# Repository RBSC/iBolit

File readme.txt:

--------------------------------------------------------------------------------
iBolit Simple Diagnostics Cartridge
Copyright (c) 2020-2022 RBSC
Last updated: 16.07.2022
--------------------------------------------------------------------------------

UPDATE from 16.07.2022
----------------------

It's recommended to update the cartridge with an overvoltage protection. See the "iBolit_fuse.jpg" image in the Pics folder!

To install the overvoltage protection, isolate pin 24 of IC1 - cut the traces on both sides of the pin. Then purchase and
solder a 5.1V 1W rated zener diode between pins 12 and 24, the cathode should be connected to pin 24. Solder resettable fuse
0.5A between C2 and pin 24 of IC1. Solder a wire between C5 and the cut off trace to supply power to the voltmeters.

This way the PLD ICs and LEDs will be protected from the overvoltage while the 5V voltmeter will show exact voltage on the slot
connector.

About
-----

iBolit is a simple diagnostics cartridge. During the previous years we've seen numerous messages from MSX users, whose computers
suddenly stopped working after being removed from the storage or after another power cycle. Many people complained about black
screens or about total power failure. It's a known fact that RAM and other elements may go bad during storing or at power-on.
Diagnosing those problems usually starts from checking the power rails, clock signals, reset signal's state and activity on data
and address bus. It has been decided to create a simple diagnostics cartridge that could help to perform the initial check of a
computer and rule out the most common problems.

The cartridge that we named "iBolit" ( see Doctor Aybolit) was created using the GAL22V10 programmable logic chips, LED assemblies
and volt/ammeters from the PC's USB socket tester dongles. There's a cartridge slot installed on the top of iBolit cartridge's
board. There one can insert any cartridge including the one with MSX diagnostics ROM (there are a few, but it would be nice to
create a universal one). The GAL firmware is very primitive - if there's a high level on input, the LED connected to the output
will light up. The cartridge is fairly cheap to build - maximum 12-15 Euro - and is relatively easy to assemble. The daughterboard
with voltmeters is detachable.

Where to buy parts
------------------

The parts for assembling the cartridge can be purchased from these sellers on AliExpress:

 - https://www.aliexpress.com/item/32929139598.html   (buy the one with gray case and USB connectors on the left and right side)
 - https://www.aliexpress.com/item/4000078359420.html (buy 2 converters)
 - https://www.aliexpress.com/item/4001336380255.html (buy 2x5 pin headers)
 - https://www.aliexpress.com/item/32890057619.html   (buy 2x5 pin connectors)
 - https://www.aliexpress.com/item/4000970562846.html (also buy blue and yellow colors)
 - https://www.aliexpress.com/item/32800771545.html   (or use a different 5mm LED)
 - https://www.aliexpress.com/item/32918831775.html   (buy 1kOhm SMD resistor assemblies)
 - https://www.aliexpress.com/item/32948284513.html   (this LED is for the -12v voltmeter)
 - https://www.aliexpress.com/item/32375666910.html   (buy 10uF and 47uF capacitors)
 - https://www.aliexpress.com/item/4001146953252.html (buy 50-pin angled slot connector)

Assembling notes
----------------

Please read the following notes carefully:

 - It's highly recommended to install ceramic capacitors everywhere on the board. For the DC-DC converters the ceramic 10uF
   capacitors are a must

 - To adapt the voltmeters to work with iBolit, you need to first carefully open the USB tester's case with a knife and remove
   the board. Then desolder both indicator panels (mark one indicator panel to know where it came from) and desolder both USB
   connectors from the board. After that solder the indicator panels back to the board, but as low as possible. And finally
   solder two 4-pin pin headers to the board, the pins will have to be forces into the board because the distance between the
   holes is not 2.54mm

 - The voltmeter with a separate red LED is for -12v, it should be installed on the lowest position of the daughterboard. See
   the reference images

 - To install a small red LED to the -12v voltmeter (this step is optional), solder the cathode to the upper GND track and
   anode to the second pin from the top. See the reference images. The LED should be a bit above the voltmeter's board

 - Please note that LED assemblies may have incorrect key position! So please always test the LED assemblies with multimeter
   in the diode testing mode to find the correct polarity. The cathode should be on the right, like marked on the board

 - The pins of both DC-DC converters should be carefully bent at 90 degree angle and the converters have to be installed
   face-down. See the reference images

 - The GAL chips need to be programmed with the firmware before use. A widespread TL866 programmer will do just fine. Use
   the .JED firmware file from the "Firmware" folder and the "GAL22V10D" chip type when programming

 - Instead of one blue and two red LED assemblies you might want to install one red and two blue LED assemblies. Make your
   own choice. It's recommended to install the yellow LED assembly at the rightmost position. If you are installing the
   green LED assembly, you need to select a different value for the resistor assembly, for example 330 Ohm instead of 1kOhm

 - Before inserting the diagnostics board into the MSX slot it's highly recommend to make sure that +5v on the slot is within
   acceptable range (not more than 6-7v!), otherwise the diagnostics board may be damaged. The device doesn't have the
   over-voltage protection on the +5v rail

 - The daughterboard with voltmeters is detachable. When it is detached, no power will be supplied to the upper cartridge slot.
   If you need to use the cartridge slot without the attached daughterboard, you need to put 5 jumpers horizontally on 5 pairs
   of pins of the connector

IMPORTANT!
----------

The RBSC provides all the files and information for free, without any liability (see the disclaimer.txt file). The provided information,
software or hardware must not be used for commercial purposes unless permitted by the RBSC. Producing a small amount of bare boards for
personal projects and selling the rest of the batch is allowed without the permission of RBSC.

When the sources of the tools are used to create alternative projects, please always mention the original source and the copyright!

Contact information
-------------------

The members of RBSC group Tnt23, Wierzbowsky, Pencioner, Ptero, GreyWolf, SuperMax and DJS3000 can be contacted via the group's e-mail
address:

info@rbsc.su

The group's coordinator could be reached via this e-mail address:

admin@rbsc.su

The group's website can be found here:

https://rbsc.su/
https://rbsc.su/ru

The RBSC's hardware repository can be found here:

https://github.com/rbsc

The RBSC's 3D model repository can be found here:

https://www.thingiverse.com/groups/rbsc/things

-= ! MSX FOREVER ! =-

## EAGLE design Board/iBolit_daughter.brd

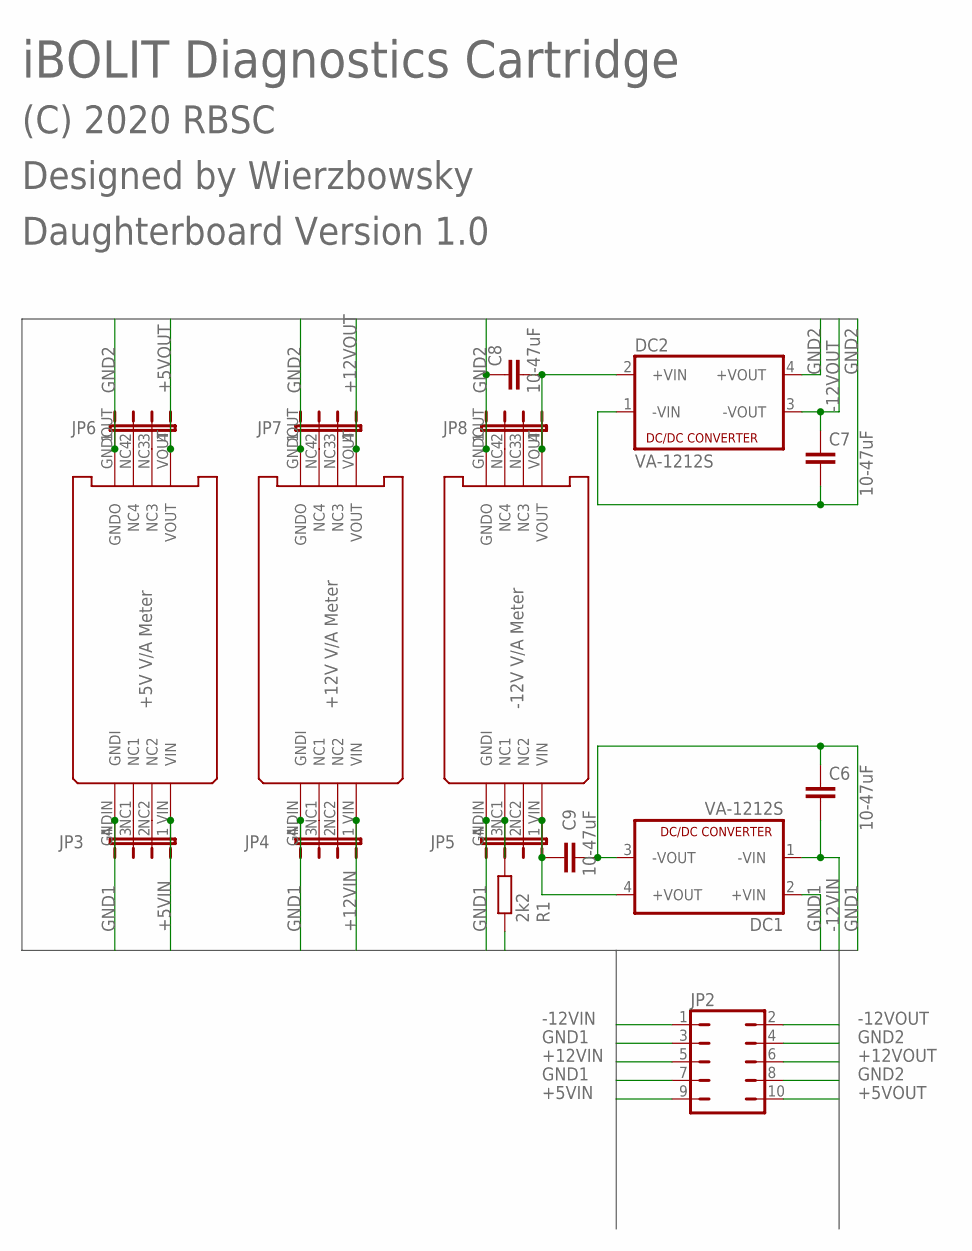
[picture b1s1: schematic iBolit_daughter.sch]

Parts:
C6, C7, C8, C9: 10-47uF; C1210
DC1, DC2: VA-1212S; 4SIL
JP2: JP5Q_CUSTOM
JP3, JP4, JP5, JP6, JP7, JP8: JP4E_CUSTOM; JP4_CUSTOM
R1: 2k2; R0805
X1, X2, X3: VA-METER; VA_METER

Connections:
+5VIN: JP2.9, JP3.1, R1.1, X1.VIN
+5VOUT: JP2.10, JP6.4, X1.VOUT
+12VCONVI: C9.1, DC1.4 (+VOUT), JP5.1, X3.VIN
+12VCONVO: C8.2, DC2.2 (+VIN), JP8.4, X3.VOUT
+12VIN: JP2.5, JP4.1, X2.VIN
+12VOUT: JP2.6, JP7.4, X2.VOUT
-12VIN: C6.2, DC1.1 (-VIN), JP2.1
-12VOUT: C7.1, DC2.3 (-VOUT), JP2.2
GND1: C6.1, C9.2, DC1.2 (+VIN), DC1.3 (-VOUT), JP2.3, JP2.7, JP3.4, JP4.4, JP5.4, X1.GNDIN (GNDI), X2.GNDIN (GNDI), X3.GNDIN (GNDI)
GND2: C7.2, C8.1, DC2.1 (-VIN), DC2.4 (+VOUT), JP2.4, JP2.8, JP6.1, JP7.1, JP8.1, X1.GNDOUT (GNDO), X2.GNDOUT (GNDO), X3.GNDOUT (GNDO)
unnamed: JP8.2, X3.NC4
unnamed: JP8.3, X3.NC3
unnamed: JP5.2, X3.NC2
unnamed: JP5.3, R1.2, X3.NC1
unnamed: JP4.2, X2.NC2
unnamed: JP3.2, X1.NC2
unnamed: JP3.3, X1.NC1
unnamed: JP6.2, X1.NC4
unnamed: JP6.3, X1.NC3
unnamed: JP7.2, X2.NC4
unnamed: JP7.3, X2.NC3
unnamed: JP4.3, X2.NC1

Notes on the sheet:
+5V V/A Meter
+12V V/A Meter
-12V V/A Meter
iBOLIT Diagnostics Cartridge
(C) 2020 RBSC
Designed by Wierzbowsky
Daughterboard Version 1.0

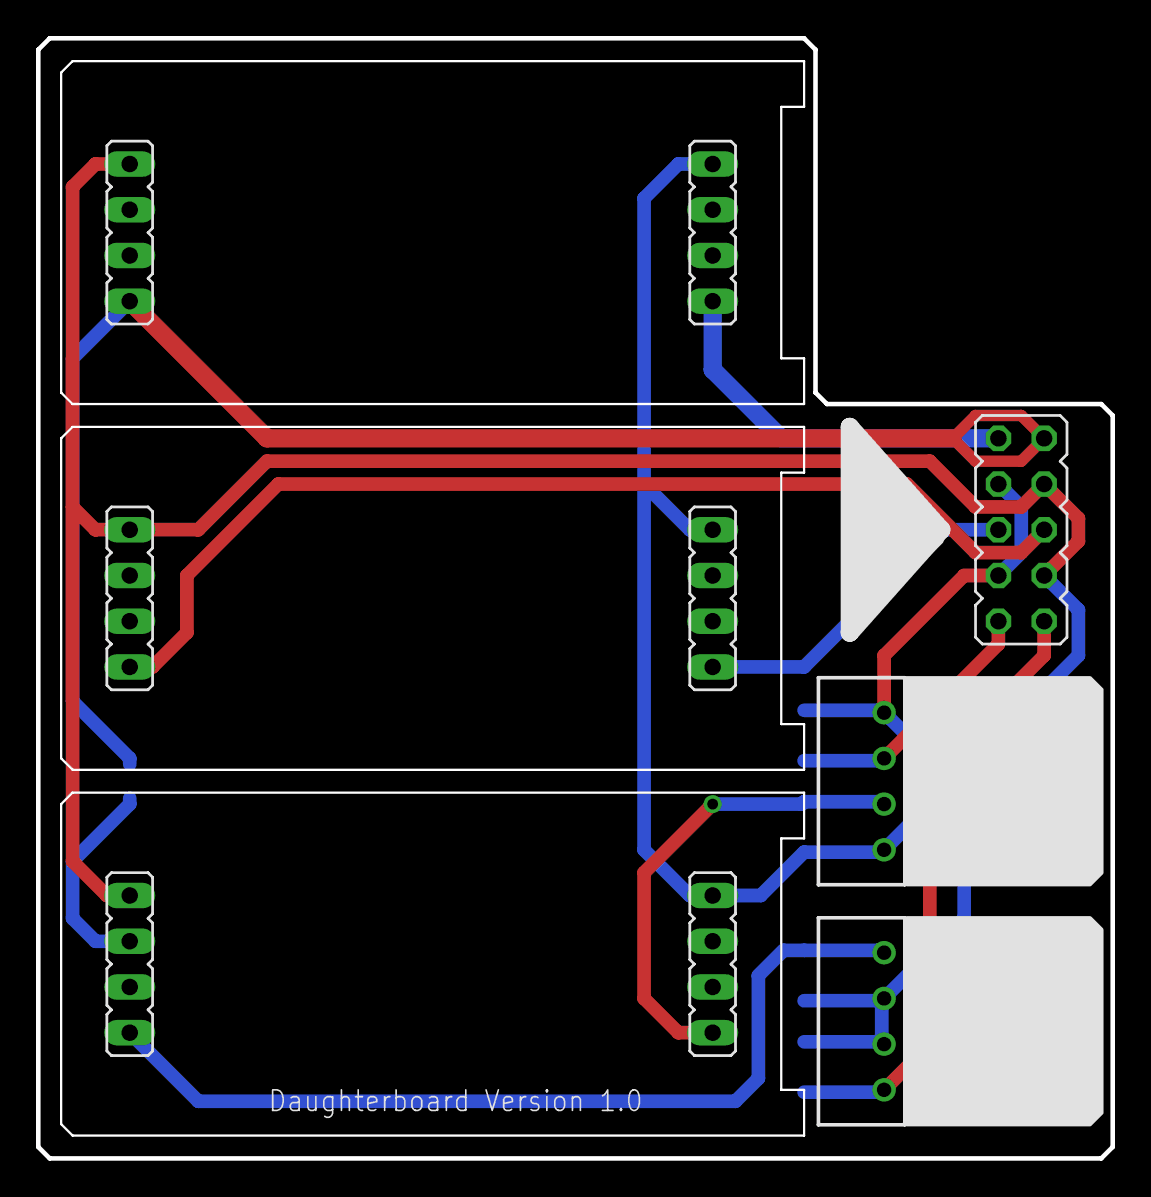
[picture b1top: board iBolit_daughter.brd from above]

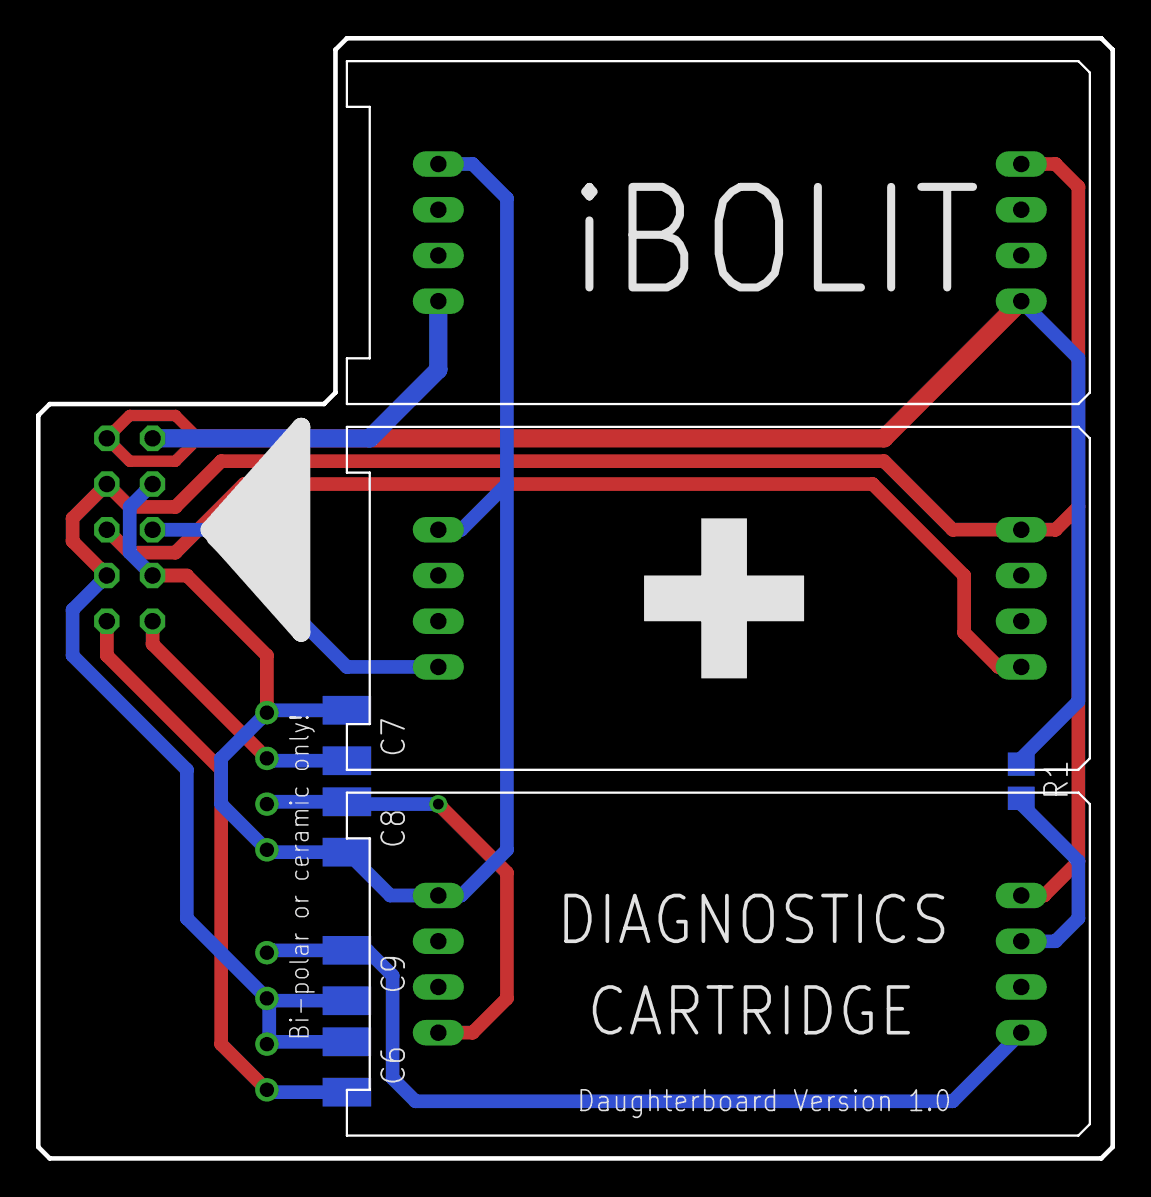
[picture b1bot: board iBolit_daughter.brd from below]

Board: 2 copper layers, 59.7 x 62.2 mm, 17 parts (5 on the bottom side), 22 nets.

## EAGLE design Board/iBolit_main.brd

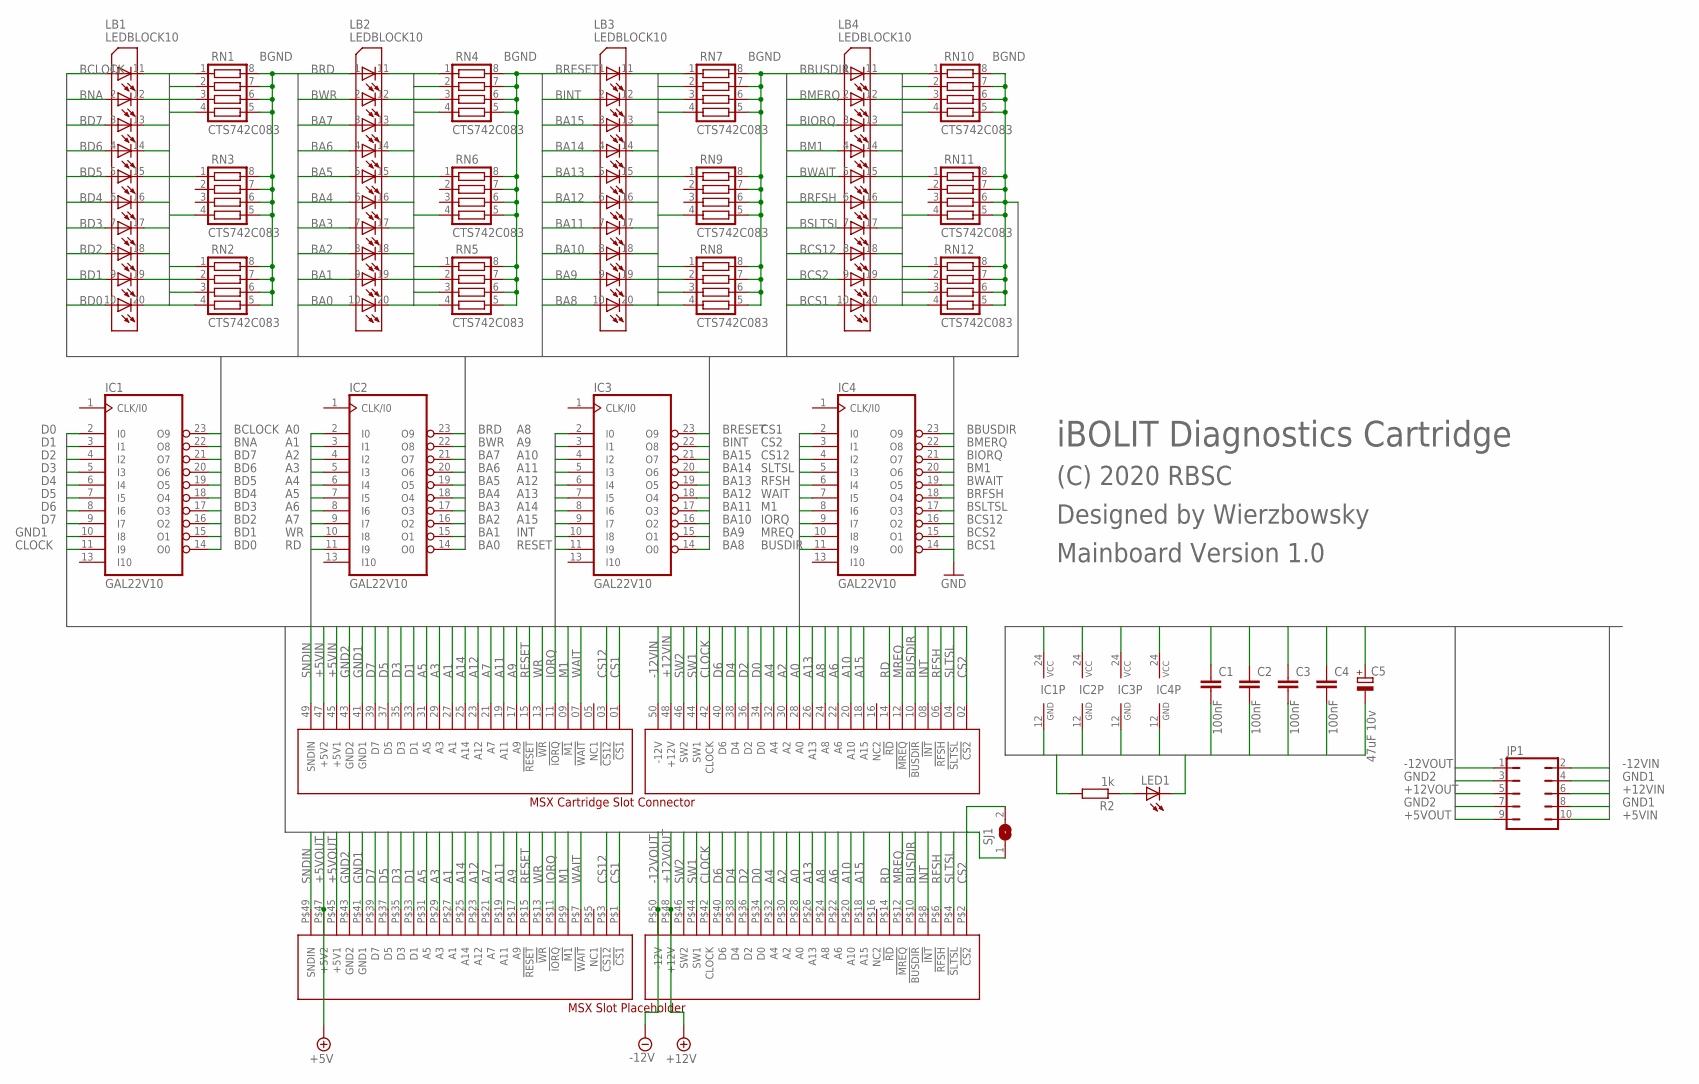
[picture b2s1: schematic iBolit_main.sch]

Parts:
C1, C2, C3, C4: 100nF; C0805
C5: 47uF 10v; SMC_B
CN1: SLOTCONN; MSX_SLOT_CON
CN2: SLOTPLACEHOLDER; MSX_SLOT_PLP
IC1, IC2, IC3, IC4: GAL22V10; DIL24-3
JP1: JP5Q_CUSTOM
LB1, LB2, LB3, LB4: LEDBLOCK10; LB10
LED1: LED5MM
R2: 1k; R0805
RN1, RN2, RN3, RN4, RN5, RN6, RN7, RN8, RN9, RN10, RN11, RN12: CTS742C083
SJ1: SJ

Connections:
1: LB1.11 (L1O), RN1.4
1A: LB2.11 (L1O), RN4.4
1B: LB3.11 (L1O), RN7.4
1C: LB4.11 (L1O), RN10.4
2: LB1.12 (L1O1), RN1.3
2A: LB2.12 (L1O1), RN4.3
2B: LB3.12 (L1O1), RN7.3
2C: LB4.12 (L1O1), RN10.3
3: LB1.13 (L1O2), RN1.2
3A: LB2.13 (L1O2), RN4.2
3B: LB3.13 (L1O2), RN7.2
3C: LB4.13 (L1O2), RN10.2
4: LB1.14 (L1O3), RN1.1
4A: LB2.14 (L1O3), RN4.1
4B: LB3.14 (L1O3), RN7.1
4C: LB4.14 (L1O3), RN10.1
5: LB1.15 (L1O4), RN3.4
5A: LB2.15 (L1O4), RN6.4
5B: LB3.15 (L1O4), RN9.4
5C: LB4.15 (L1O4), RN11.4
6: LB1.16 (L1O5), RN3.1
6A: LB2.16 (L1O5), RN6.1
6B: LB3.16 (L1O5), RN9.1
6C: LB4.16 (L1O5), RN11.1
7: LB1.17 (L1O6), RN2.4
7A: LB2.17 (L1O6), RN5.4
7B: LB3.17 (L1O6), RN8.4
7C: LB4.17 (L1O6), RN12.4
8: LB1.18 (L1O7), RN2.3
8A: LB2.18 (L1O7), RN5.3
8B: LB3.18 (L1O7), RN8.3
8C: LB4.18 (L1O7), RN12.3
9: LB1.19 (L1O8), RN2.2
9A: LB2.19 (L1O8), RN5.2
9B: LB3.19 (L1O8), RN8.2
9C: LB4.19 (L1O8), RN12.2
10: LB1.20 (L1O9), RN2.1
10A: LB2.20 (L1O9), RN5.1
10B: LB3.20 (L1O9), RN8.1
10C: LB4.20 (L1O9), RN12.1
+5VIN: C1.1, C2.1, C3.1, C4.1, C5.+, CN1.45 (+5V1), CN1.47 (+5V2), IC1.24 (VCC), IC2.24 (VCC), IC3.24 (VCC), IC4.24 (VCC), JP1.10, R2.2
+5VOUT: CN2.P$45 (+5V1), CN2.P$47 (+5V2), JP1.9
+12VIN: CN1.48 (+12V), JP1.6
+12VOUT: CN2.P$48 (+12V), JP1.5
-12VIN: CN1.50 (-12V), JP1.2
-12VOUT: CN2.P$50 (-12V), JP1.1
A0: CN1.28 (A0), CN2.P$28 (A0), IC2.2 (I0)
A1: CN1.27 (A1), CN2.P$27 (A1), IC2.3 (I1)
A2: CN1.30 (A2), CN2.P$30 (A2), IC2.4 (I2)
A3: CN1.29 (A3), CN2.P$29 (A3), IC2.5 (I3)
A4: CN1.32 (A4), CN2.P$32 (A4), IC2.6 (I4)
A5: CN1.31 (A5), CN2.P$31 (A5), IC2.7 (I5)
A6: CN1.22 (A6), CN2.P$22 (A6), IC2.8 (I6)
A7: CN1.21 (A7), CN2.P$21 (A7), IC2.9 (I7)
A8: CN1.24 (A8), CN2.P$24 (A8), IC3.2 (I0)
A9: CN1.17 (A9), CN2.P$17 (A9), IC3.3 (I1)
A10: CN1.20 (A10), CN2.P$20 (A10), IC3.4 (I2)
A11: CN1.19 (A11), CN2.P$19 (A11), IC3.5 (I3)
A12: CN1.23 (A12), CN2.P$23 (A12), IC3.6 (I4)
A13: CN1.26 (A13), CN2.P$26 (A13), IC3.7 (I5)
A14: CN1.25 (A14), CN2.P$25 (A14), IC3.8 (I6)
A15: CN1.18 (A15), CN2.P$18 (A15), IC3.9 (I7)
BA0: IC2.14 (O0), LB2.10 (L1I9)
BA1: IC2.15 (O1), LB2.9 (L1I8)
BA2: IC2.16 (O2), LB2.8 (L1I7)
BA3: IC2.17 (O3), LB2.7 (L1I6)
BA4: IC2.18 (O4), LB2.6 (L1I5)
BA5: IC2.19 (O5), LB2.5 (L1I4)
BA6: IC2.20 (O6), LB2.4 (L1I3)
BA7: IC2.21 (O7), LB2.3 (L1I2)
BA8: IC3.14 (O0), LB3.10 (L1I9)
BA9: IC3.15 (O1), LB3.9 (L1I8)
BA10: IC3.16 (O2), LB3.8 (L1I7)
BA11: IC3.17 (O3), LB3.7 (L1I6)
BA12: IC3.18 (O4), LB3.6 (L1I5)
BA13: IC3.19 (O5), LB3.5 (L1I4)
BA14: IC3.20 (O6), LB3.4 (L1I3)
BA15: IC3.21 (O7), LB3.3 (L1I2)
BBUSDIR: IC4.23 (O9), LB4.1 (L1I)
BCLOCK: IC1.23 (O9), LB1.1 (L1I)
BCS1: IC4.14 (O0), LB4.10 (L1I9)
BCS2: IC4.15 (O1), LB4.9 (L1I8)
BCS12: IC4.16 (O2), LB4.8 (L1I7)
BD0: IC1.14 (O0), LB1.10 (L1I9)
BD1: IC1.15 (O1), LB1.9 (L1I8)
BD2: IC1.16 (O2), LB1.8 (L1I7)
BD3: IC1.17 (O3), LB1.7 (L1I6)
BD4: IC1.18 (O4), LB1.6 (L1I5)
BD5: IC1.19 (O5), LB1.5 (L1I4)
BD6: IC1.20 (O6), LB1.4 (L1I3)
BD7: IC1.21 (O7), LB1.3 (L1I2)
BGND: RN1.5, RN1.6, RN1.7, RN1.8, RN2.5, RN2.6, RN2.7, RN2.8, RN3.5, RN3.6, RN3.7, RN3.8, RN4.5, RN4.6, RN4.7, RN4.8, RN5.5, RN5.6, RN5.7, RN5.8, RN6.5, RN6.6, RN6.7, RN6.8, RN7.5, RN7.6, RN7.7, RN7.8, RN8.5, RN8.6, RN8.7, RN8.8, RN9.5, RN9.6, RN9.7, RN9.8, RN10.5, RN10.6, RN10.7, RN10.8, RN11.5, RN11.6, RN11.7, RN11.8, RN12.5, RN12.6, RN12.7, RN12.8
BINT: IC3.22 (O8), LB3.2 (L1I1)
BIORQ: IC4.21 (O7), LB4.3 (L1I2)
BM1: IC4.20 (O6), LB4.4 (L1I3)
BMERQ: IC4.22 (O8), LB4.2 (L1I1)
BNA: IC1.22 (O8), LB1.2 (L1I1)
BRD: IC2.23 (O9), LB2.1 (L1I)
BRESET: IC3.23 (O9), LB3.1 (L1I)
BRFSH: IC4.18 (O4), LB4.6 (L1I5)
BSLTSL: IC4.17 (O3), LB4.7 (L1I6)
BUSDIR: CN1.10 (!BUSDIR), CN2.P$10 (!BUSDIR), IC4.11 (I9)
BWAIT: IC4.19 (O5), LB4.5 (L1I4)
BWR: IC2.22 (O8), LB2.2 (L1I1)
CLOCK: CN1.42 (CLOCK), CN2.P$42 (CLOCK), IC1.11 (I9)
CS1: CN1.01 (!CS1), CN2.P$1 (!CS1), IC4.2 (I0)
CS2: CN1.02 (!CS2), CN2.P$2 (!CS2), IC4.3 (I1)
CS12: CN1.03 (!CS12), CN2.P$3 (!CS12), IC4.4 (I2)
D0: CN1.34 (D0), CN2.P$34 (D0), IC1.2 (I0)
D1: CN1.33 (D1), CN2.P$33 (D1), IC1.3 (I1)
D2: CN1.36 (D2), CN2.P$36 (D2), IC1.4 (I2)
D3: CN1.35 (D3), CN2.P$35 (D3), IC1.5 (I3)
D4: CN1.38 (D4), CN2.P$38 (D4), IC1.6 (I4)
D5: CN1.37 (D5), CN2.P$37 (D5), IC1.7 (I5)
D6: CN1.40 (D6), CN2.P$40 (D6), IC1.8 (I6)
D7: CN1.39 (D7), CN2.P$39 (D7), IC1.9 (I7)
GND1: C1.2, C2.2, C3.2, C4.2, C5.-, CN1.41 (GND1), CN2.P$41 (GND1), IC1.10 (I8), IC1.12 (GND), IC2.12 (GND), IC3.12 (GND), IC4.12 (GND), JP1.4, JP1.8, LED1.K (C)
GND2: CN1.43 (GND2), CN2.P$43 (GND2), JP1.3, JP1.7
INT: CN1.08 (!INT), CN2.P$8 (!INT), IC3.10 (I8)
IORQ: CN1.11 (!IORQ), CN2.P$11 (!IORQ), IC4.9 (I7)
M1: CN1.09 (!M1), CN2.P$9 (!M1), IC4.8 (I6)
MREQ: CN1.12 (!MREQ), CN2.P$12 (!MREQ), IC4.10 (I8)
unnamed: LED1.A, R2.1
RD: CN1.14 (!RD), CN2.P$14 (!RD), IC2.11 (I9)
RESET: CN1.15 (!RESET), CN2.P$15 (!RESET), IC3.11 (I9)
RFSH: CN1.06 (!RFSH), CN2.P$6 (!RFSH), IC4.6 (I4)
SLTSL: CN1.04 (!SLTSL), CN2.P$4 (!SLTSL), IC4.5 (I3)
SNDIN: CN1.49 (SNDIN), CN2.P$49 (SNDIN)
SW1: CN1.44 (SW1), CN2.P$44 (SW1), SJ1.2
SW2: CN1.46 (SW2), CN2.P$46 (SW2), SJ1.1
WAIT: CN1.07 (!WAIT), CN2.P$7 (!WAIT), IC4.7 (I5)
WR: CN1.13 (!WR), CN2.P$13 (!WR), IC2.10 (I8)

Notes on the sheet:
iBOLIT Diagnostics Cartridge
(C) 2020 RBSC
Designed by Wierzbowsky
Mainboard Version 1.0

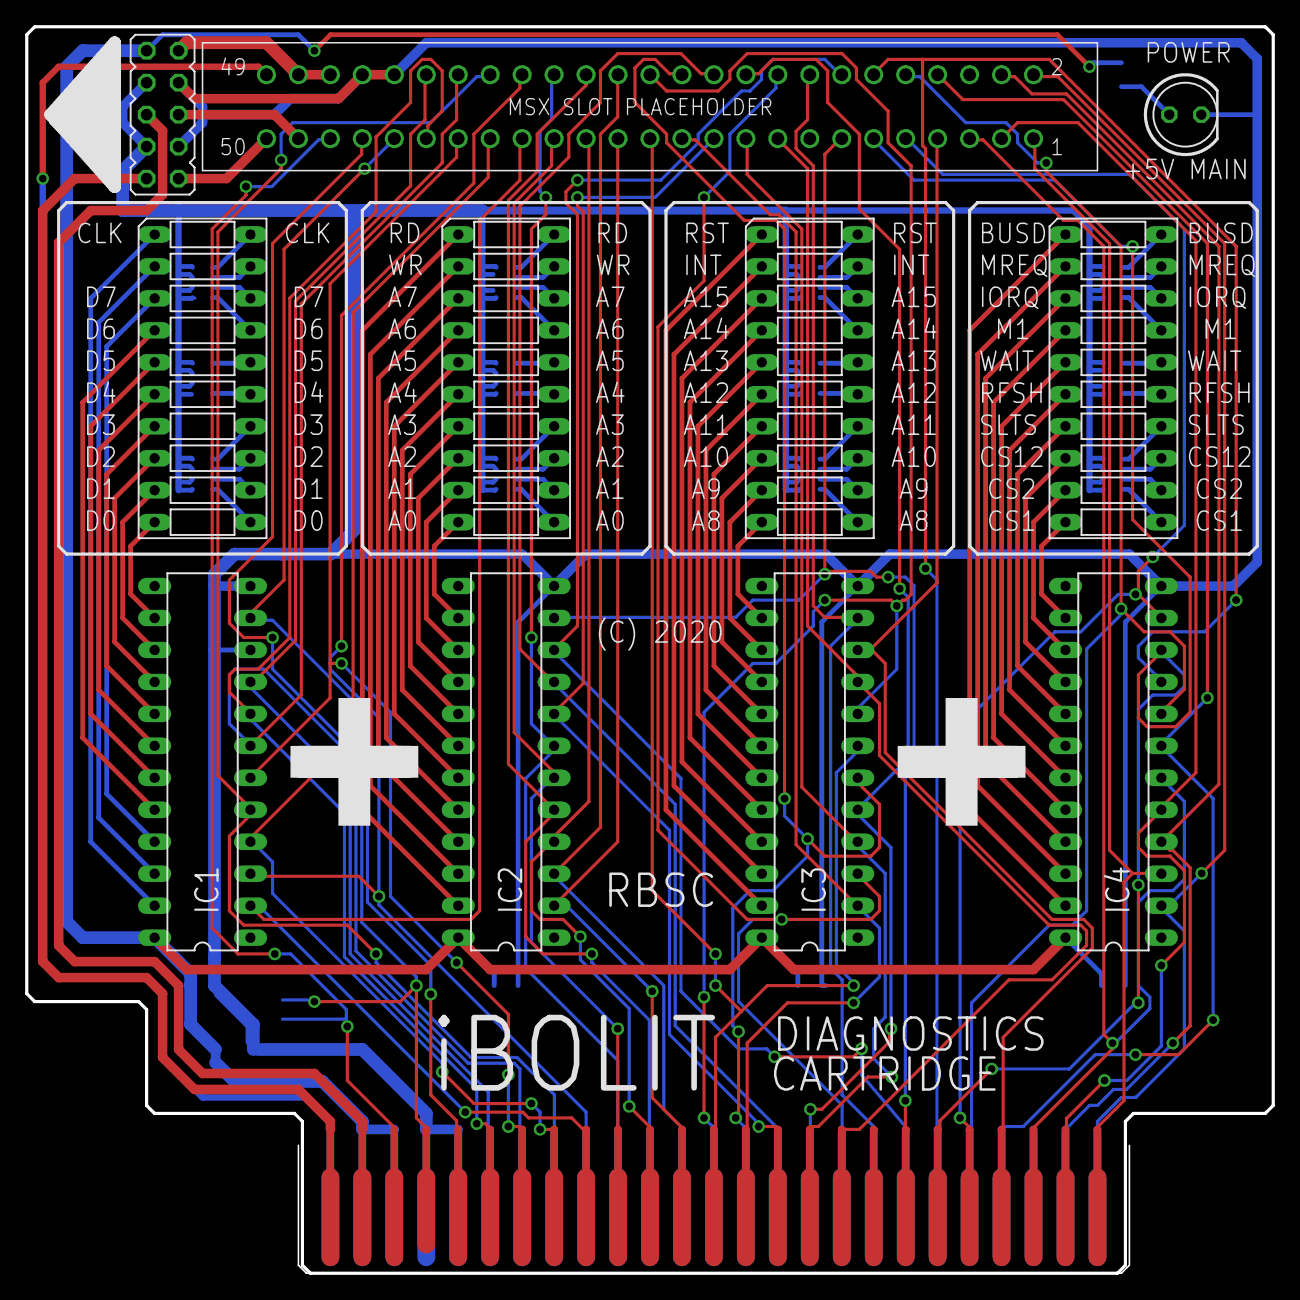
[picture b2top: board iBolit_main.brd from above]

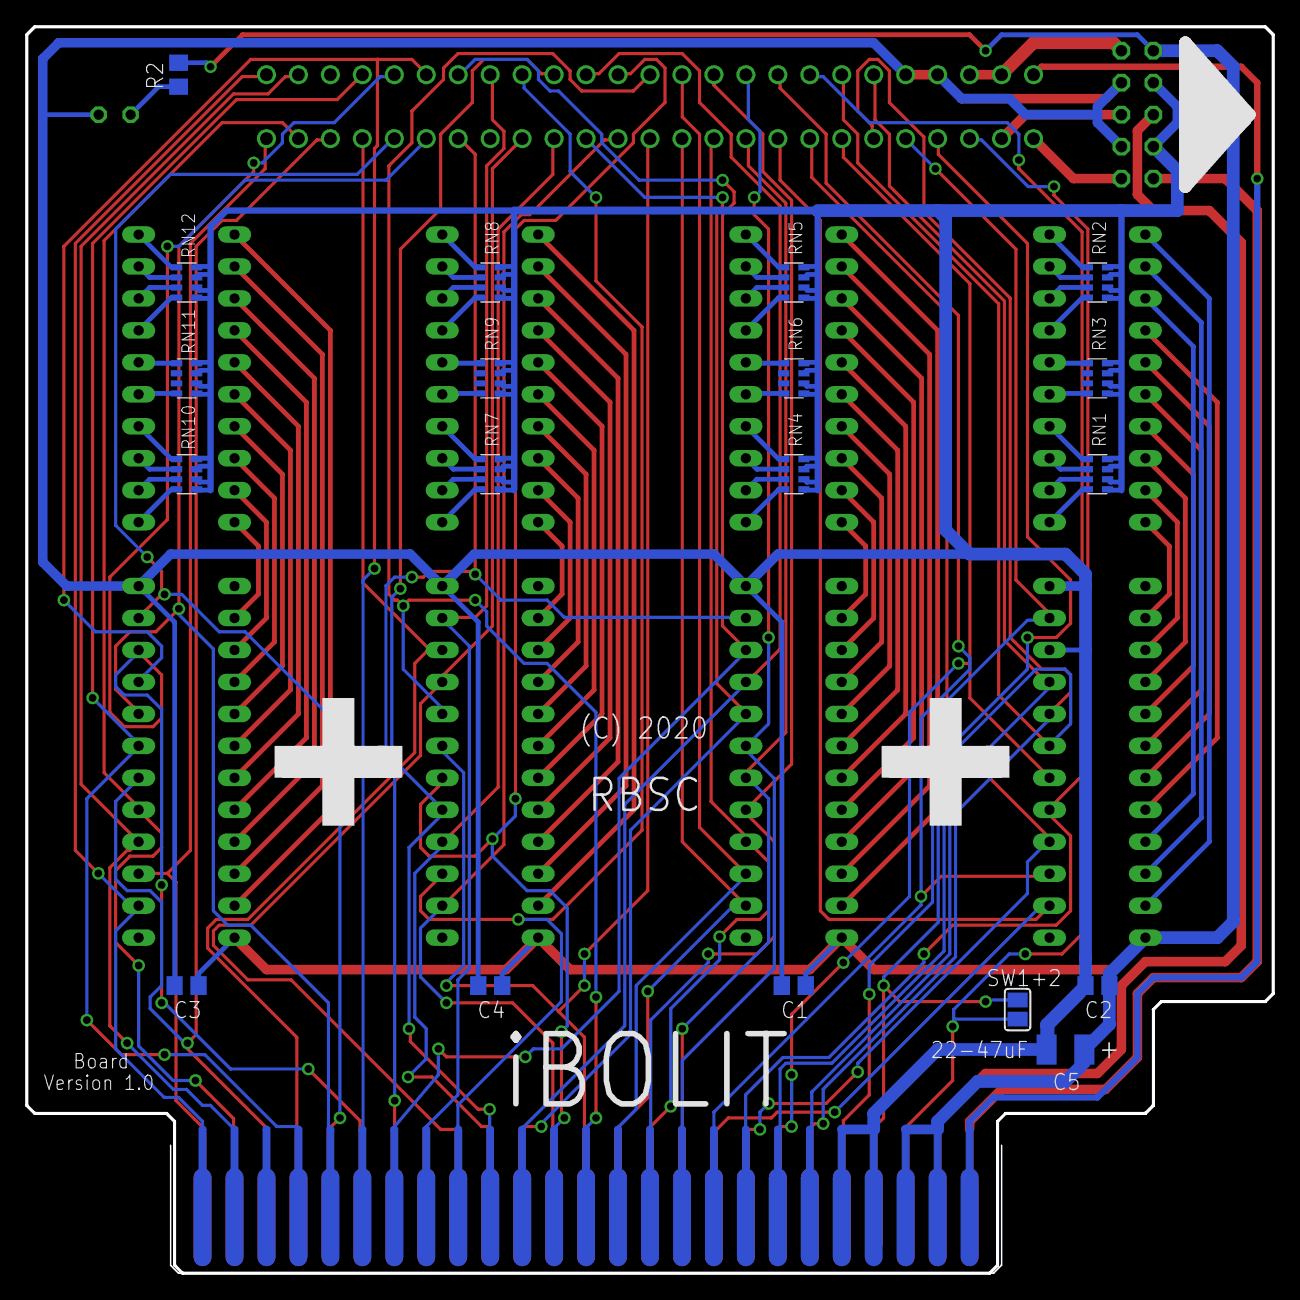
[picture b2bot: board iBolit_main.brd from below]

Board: 2 copper layers, 99.1 x 99.1 mm, 31 parts (19 on the bottom side), 132 nets.

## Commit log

2021-03-14 :circus_tent: Added .gitattributes & .gitignore files
2021-03-14 Initial release 14.03.2021
    Initial release 14.03.2021
2021-03-16 Updated 16.03.2021
    Updated the readme.txt file
2021-03-18 Updated 18.03.2021
    Updated readme, fixed typo on daughterboard
2021-03-26 Updated 26.03.2021
    Updated partslist with pin header info
2021-04-09 Updated 09.04.2021
    Updated readme and partslist to include slot connector info
2021-09-16 Updated 16.09.2021
    Updated schematics
2022-07-16 Updated 16.07.2022
    Added overvoltage protection info and image
